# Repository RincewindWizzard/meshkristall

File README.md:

# meshkristall

This project aims to provide a simple board with four buttons and a RGB LED, 
which is capable to communicate over 433 Mhz for interactive radio frequency light installations.

I am planning a case like [this](https://www.youtube.com/watch?v=kgPghSJhkzU) for the board.
The current sketch sends button events over 433 Mhz radio to all other boards. 
Three buttons are connected to the red, green and blue LEDs and the fourth is connected to the remote beepers.
If you press the color buttons, the LED is lit and the current state of buttons is send to the other boards, which show the same color. 
The beeper is only triggered in the remote boards.

Currently the range is only ca. 10 meters, which is nice but not what I need.
As I want to use them as "color telegraphs", they should have a range of 1 kilometer or more.
I will try 2.4 Ghz next. Maybe that works better.

You will find all schematics in this repository.

# Parts list
- [FS1000A](http://www.ebay.de/itm/5X-433-Mhz-RF-Sender-Empfanger-Receiver-Modul-Wireless-Transmitter-MX-05V-DC5V/252441619018?_trksid=p2047675.c100005.m1851&_trkparms=aid%3D222007%26algo%3DSIC.MBE%26ao%3D1%26asc%3D39275%26meid%3D255992112e8d4b46b61d8e5a2a8e73f5%26pid%3D100005%26rk%3D2%26rkt%3D6%26sd%3D322037467813) (433Mhz reciever)
- [XY-MK-5V](http://www.ebay.de/itm/5X-433-Mhz-RF-Sender-Empfanger-Receiver-Modul-Wireless-Transmitter-MX-05V-DC5V/252441619018?_trksid=p2047675.c100005.m1851&_trkparms=aid%3D222007%26algo%3DSIC.MBE%26ao%3D1%26asc%3D39275%26meid%3D255992112e8d4b46b61d8e5a2a8e73f5%26pid%3D100005%26rk%3D2%26rkt%3D6%26sd%3D322037467813)
- [Arduino nano](http://www.ebay.de/itm/MINI-USB-Nano-V3-0-ATmega328P-CH340G-5V-16M-Compatible-Arduino-Nano-V3-0-CY-/191760234382?hash=item2ca5ccf78e:g:Wp8AAOSwYaFWb2dA)

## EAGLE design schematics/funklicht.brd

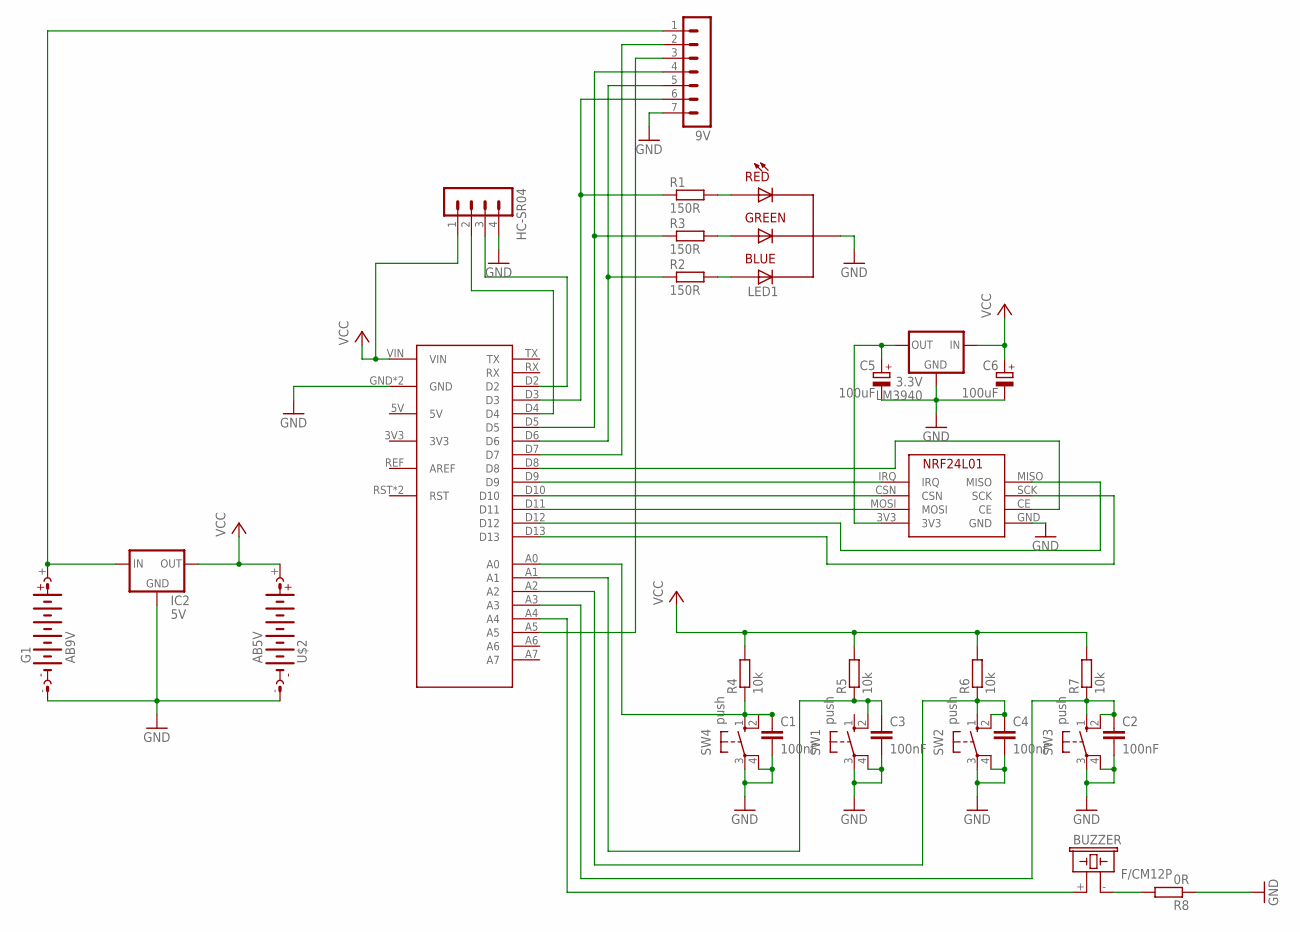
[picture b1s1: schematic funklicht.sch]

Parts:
3.3V: LM3940; 78XXS
9V: MA07-1
BUZZER: F/CM12P
C1, C2, C3, C4: 100nF; C025-024X044
C5, C6: 100uF; TT2D6
G1: AB9V
HC-SR04: MA04-1
IC2: 5V; 78XXS
LED1: LED5MM
R1, R2, R3: 150R; 0207/10
R4, R5, R6, R7: 10k; 0207/10
R8: 0R; 0207/10
SW1, SW2, SW3, SW4: push; B3F-10XX
U$1: ARDUINO_PLATINE
U$2: AB5V; AB9V
U$3: NRF24L01

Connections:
3V3: 3.3V.OUT, C5.+, U$3.3V3
BLUE: LED1.BLUE, R2.2
GND: 3.3V.GND, 9V.7, C1.2, C2.2, C3.2, C4.2, C5.-, C6.-, G1.-, HC-SR04.4, IC2.GND, LED1.GND, R8.1, SW1.3, SW1.4 (P1), SW2.3, SW2.4 (P1), SW3.3, SW3.4 (P1), SW4.3, SW4.4 (P1), U$1.GND, U$1.GND1 (GND), U$2.-, U$3.GND
GREEN: LED1.GREEN, R3.2
unnamed: C1.1, R4.1, SW4.1 (S), SW4.2 (S1), U$1.A0
unnamed: 9V.5, R2.1, U$1.D6
unnamed: U$1.D12, U$3.MISO
unnamed: U$1.D9, U$3.IRQ
unnamed: U$1.D13, U$3.SCK
unnamed: U$1.D11, U$3.MOSI
unnamed: U$1.D10, U$3.CSN
unnamed: U$1.D8, U$3.CE
unnamed: 9V.4, R3.1, U$1.D5
unnamed: 9V.6, R1.1, U$1.D3
unnamed: HC-SR04.3, U$1.D2
unnamed: HC-SR04.2, U$1.D4
unnamed: C3.1, R5.1, SW1.2 (S1), U$1.A1
unnamed: C4.1, R6.1, SW2.1 (S), SW2.2 (S1), U$1.A2
unnamed: C2.1, R7.1, SW3.1 (S), SW3.2 (S1), U$1.A3
unnamed: BUZZER.+ (1), U$1.A4
unnamed: BUZZER.- (2), R8.2
unnamed: 9V.1, G1.+, IC2.IN
unnamed: 9V.2, U$1.D7
unnamed: 9V.3, U$1.A5
RED: LED1.RED, R1.2
VCC: 3.3V.IN, C6.+, HC-SR04.1, IC2.OUT, R4.2, R5.2, R6.2, R7.2, U$1.VIN, U$2.+

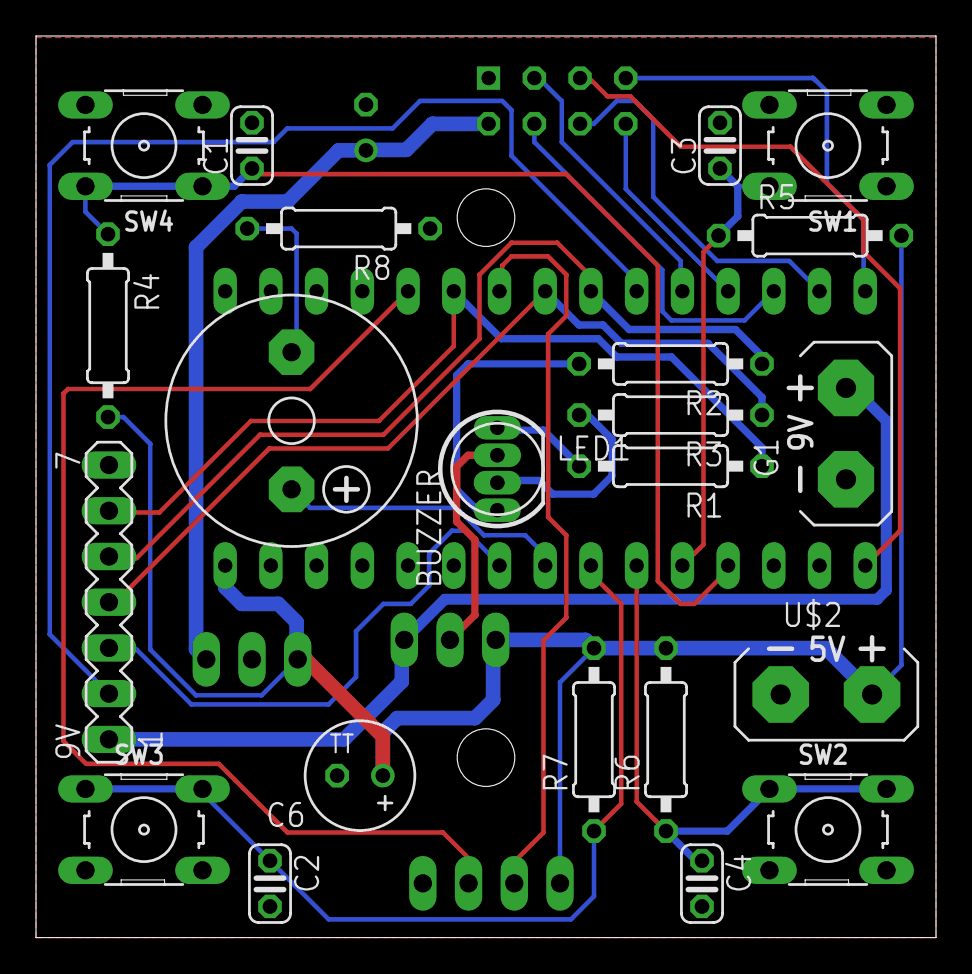
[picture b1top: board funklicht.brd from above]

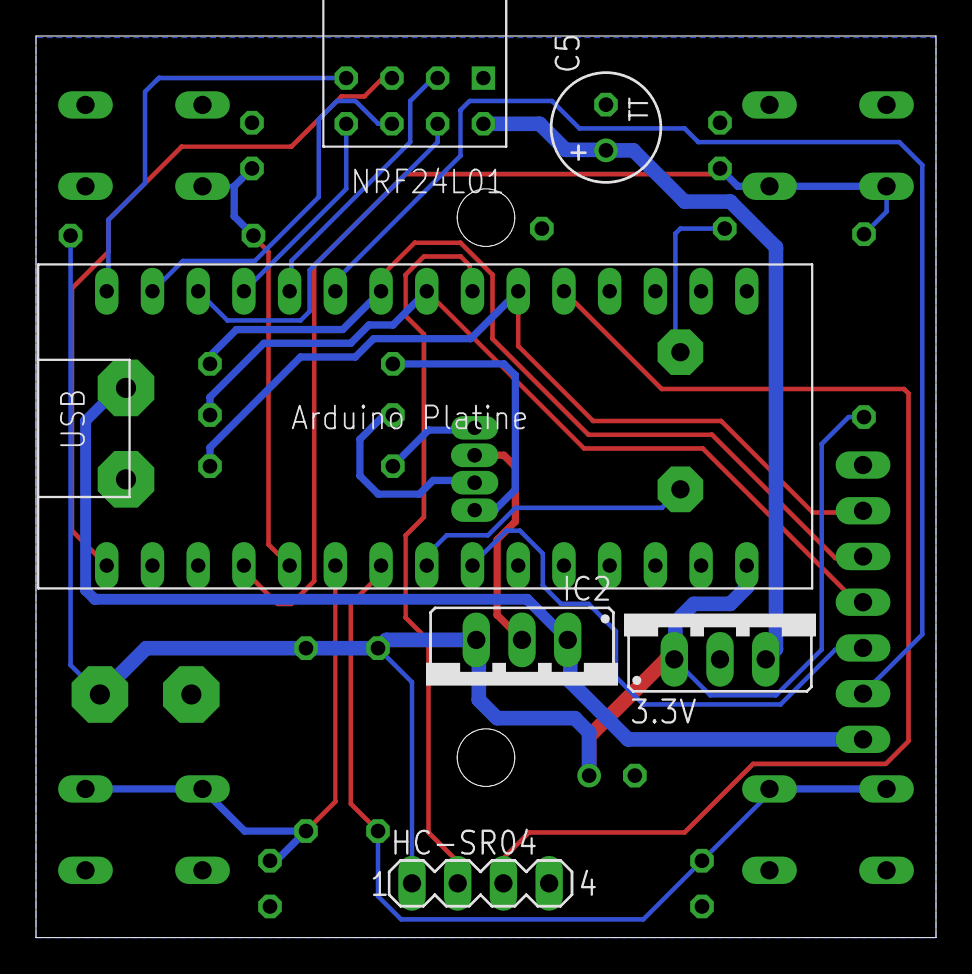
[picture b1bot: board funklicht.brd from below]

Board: 2 copper layers, 50.0 x 50.1 mm, 28 parts (6 on the bottom side), 26 nets.

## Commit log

2016-10-06 prototyp
2016-10-07 added readme
2016-10-09 kommafehler
2016-10-09 schematics done
2016-10-09 hand routed board
2016-10-09 fertiges platinenlayout
2016-10-09 Readme
2016-10-10 BoardLayout Picture
2016-10-10 record animations
2016-10-10 sending animations
2016-12-28 Added Schematics and Board Screenshot
